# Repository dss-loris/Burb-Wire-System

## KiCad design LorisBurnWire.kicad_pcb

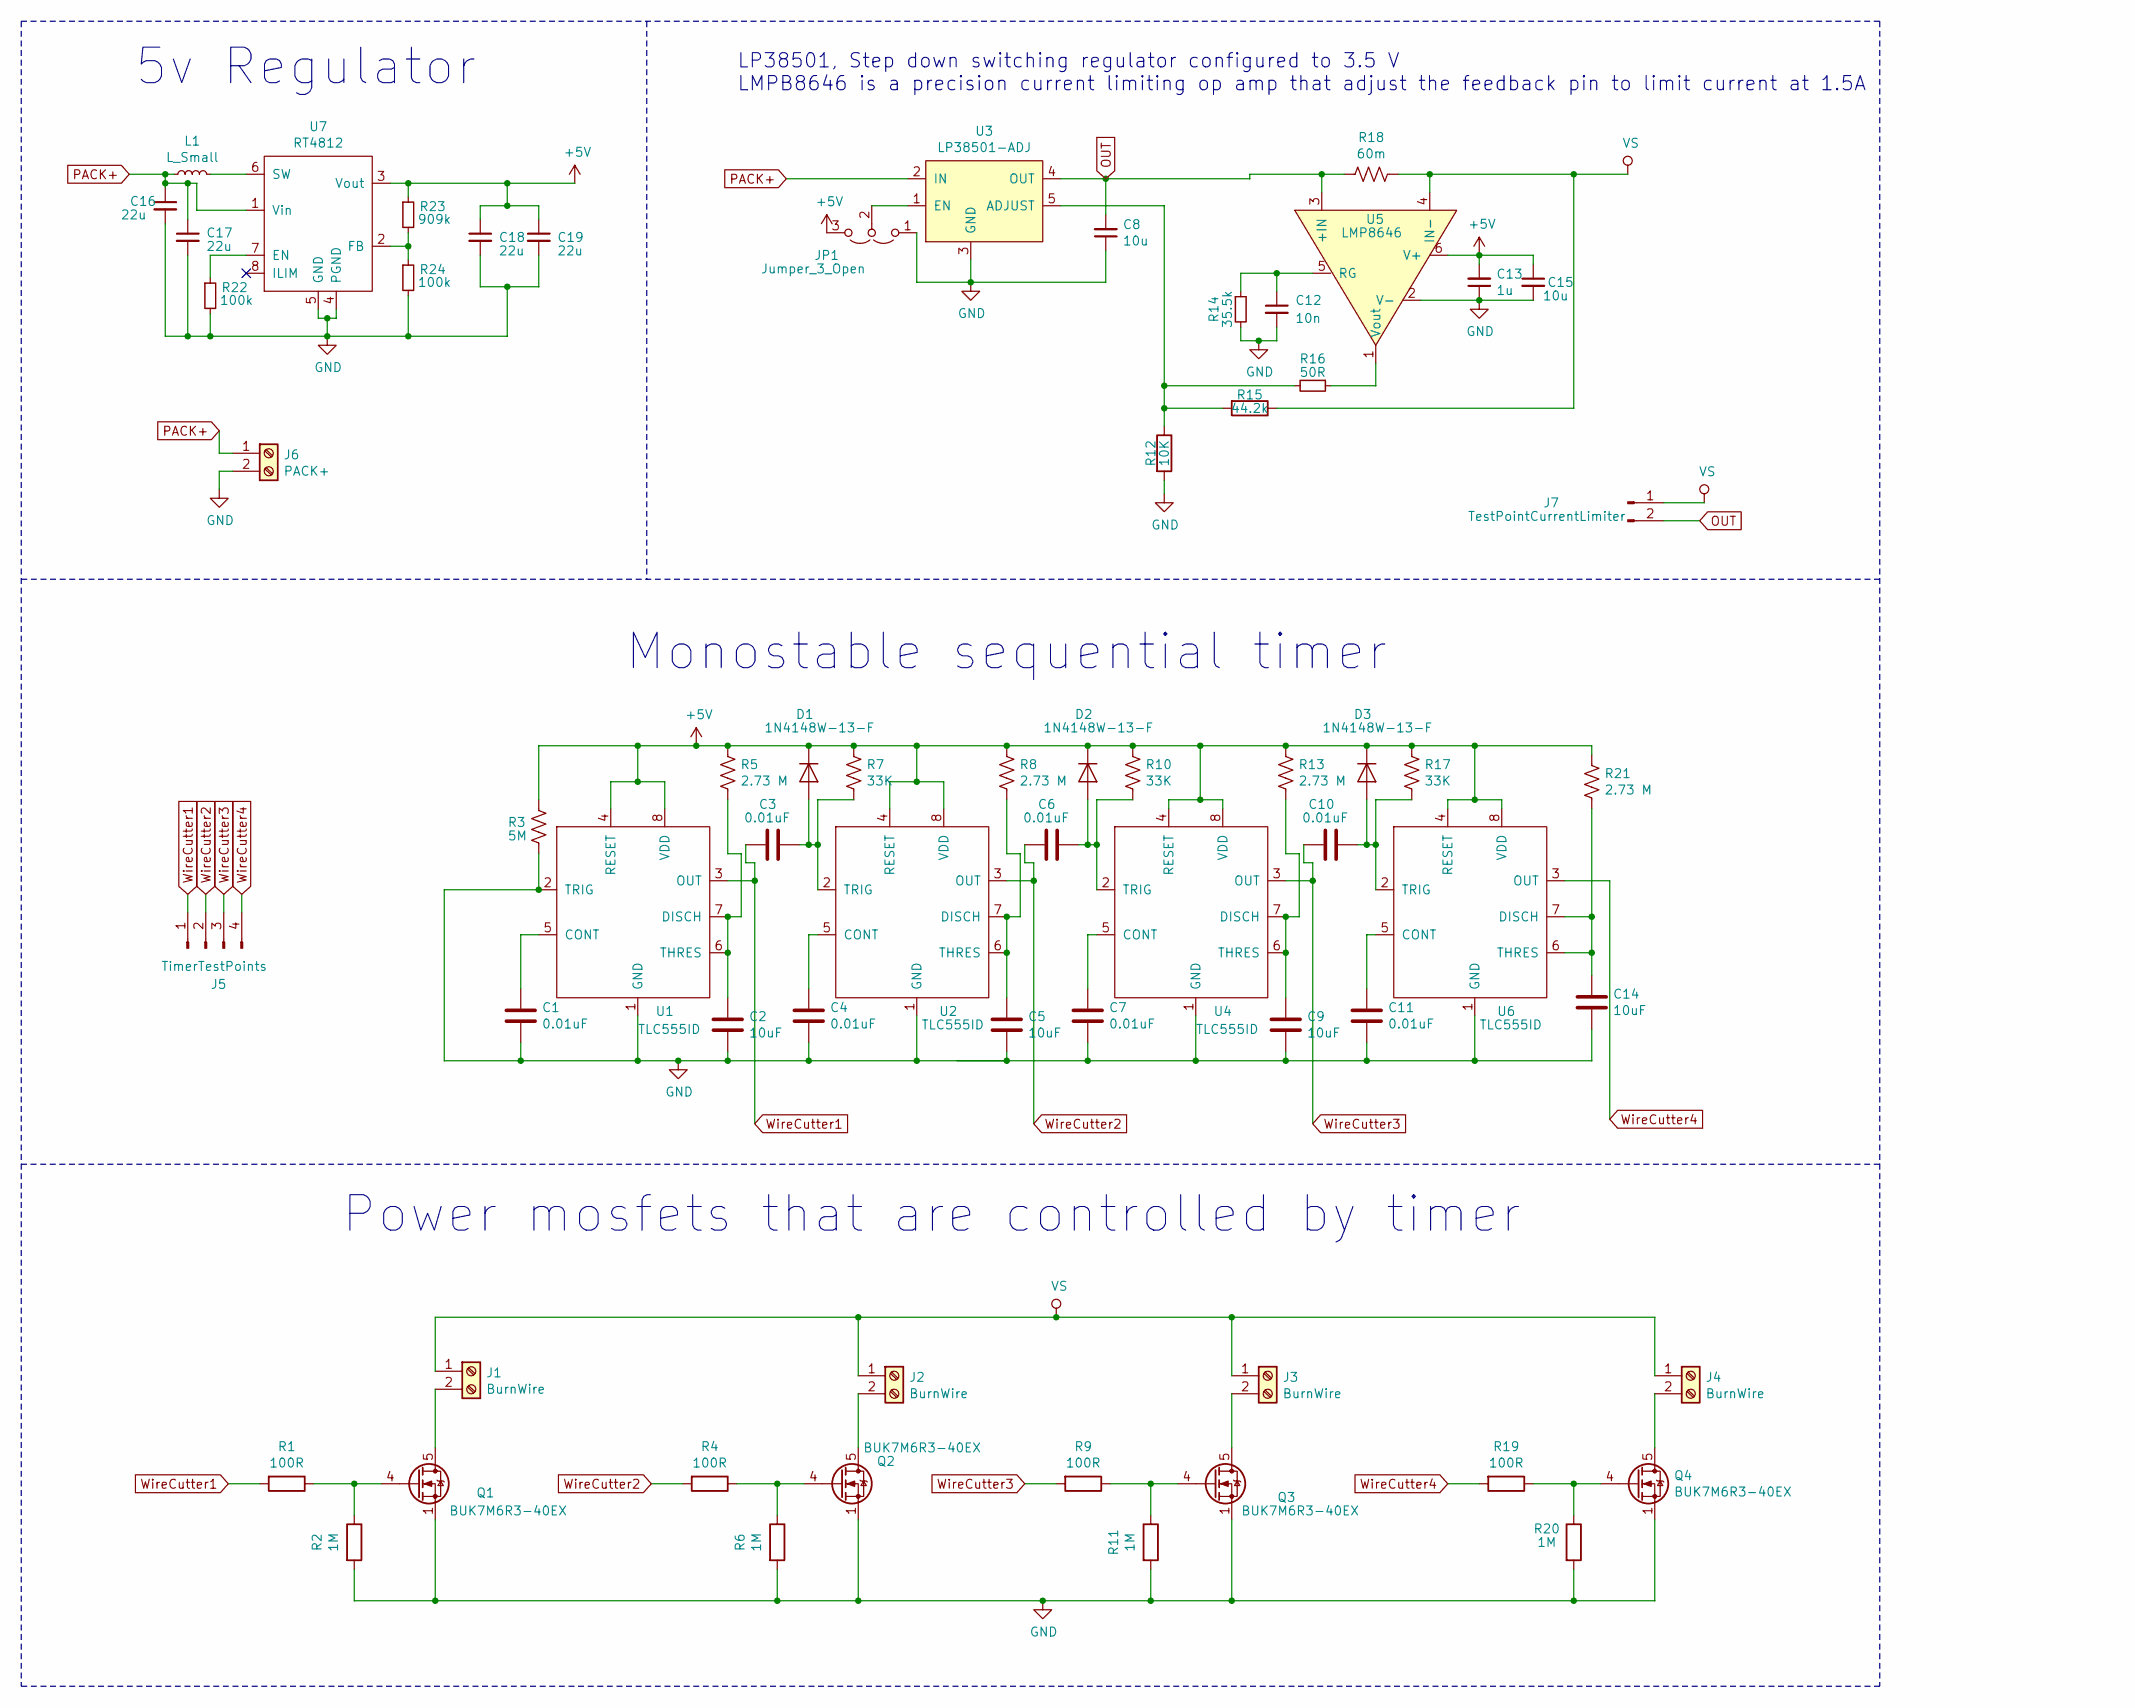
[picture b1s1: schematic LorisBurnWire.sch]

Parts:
C1, C3, C4, C6, C7, C10, C11: 0.01uF; C_1206_3216Metric_Pad1.42x1.75mm_HandSolder
C2, C5, C9, C14: 10uF; C_1206_3216Metric_Pad1.42x1.75mm_HandSolder
C8, C15: 10u; C_1206_3216Metric_Pad1.42x1.75mm_HandSolder
C12: 10n; C_1206_3216Metric_Pad1.42x1.75mm_HandSolder
C13: 1u; C_1206_3216Metric_Pad1.42x1.75mm_HandSolder
C16, C17, C18, C19: 22u; C_1206_3216Metric_Pad1.42x1.75mm_HandSolder
D1, D2, D3: 1N4148W-13-F; D_SOD-123
J1, J2, J3, J4: BurnWire; TE_282837-2
J5: TimerTestPoints; PinHeader_1x04_P2.54mm_Vertical
J6: PACK+; TE_282837-2
J7: TestPointCurrentLimiter; PinHeader_1x02_P2.54mm_Vertical
JP1: Jumper_3_Open; PinHeader_1x03_P2.54mm_Vertical
L1: L_Small; SPM6530T-3R3M; MFG Part Number SPM6530T-3R3M
Q1, Q2, Q3, Q4: BUK7M6R3-40EX; LFPAK33
R1, R4, R9, R19: 100R; R_1206_3216Metric_Pad1.42x1.75mm_HandSolder
R2, R6, R11, R20: 1M; R_1206_3216Metric_Pad1.42x1.75mm_HandSolder
R3: 5M; R_1206_3216Metric_Pad1.42x1.75mm_HandSolder
R5, R8, R13, R21: 2.73 M; R_1206_3216Metric_Pad1.42x1.75mm_HandSolder
R7, R10, R17: 33K; R_1206_3216Metric_Pad1.42x1.75mm_HandSolder
R12: 10K; R_1206_3216Metric_Pad1.42x1.75mm_HandSolder
R14: 35.5k; R_1206_3216Metric_Pad1.42x1.75mm_HandSolder
R15: 44.2k; R_1206_3216Metric_Pad1.42x1.75mm_HandSolder
R16: 50R; R_1206_3216Metric_Pad1.42x1.75mm_HandSolder
R18: 60m; R_1206_3216Metric_Pad1.42x1.75mm_HandSolder
R22, R24: 100k; R_1206_3216Metric_Pad1.42x1.75mm_HandSolder
R23: 909k; R_1206_3216Metric_Pad1.42x1.75mm_HandSolder
U1, U2, U4, U6: TLC555ID; SOIC-8_3.9x4.9mm_P1.27mm
U3: LP38501-ADJ; TO-263-5_TabPin3
U5: LMP8646; TSOT-23-6_HandSoldering
U7: RT4812; TSOT-23-8_HandSoldering

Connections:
+5V: C13.2, C15.1, C18.1, C19.1, D1.1 (K), D2.1 (K), D3.1 (K), JP1.3 (B), R3.1, R5.1, R7.1, R8.1, R10.1, R13.1, R17.1, R21.1, R23.1, U1.4 (RESET), U1.8 (VDD), U2.4 (RESET), U2.8 (VDD), U4.4 (RESET), U4.8 (VDD), U5.6 (V+), U6.4 (RESET), U6.8 (VDD), U7.3 (Vout)
GND: C1.2, C2.2, C4.2, C5.2, C7.2, C8.1, C9.2, C11.2, C12.2, C13.1, C14.2, C15.2, C16.2, C17.2, C18.2, C19.2, J6.2, JP1.1 (A), Q1.1 (S), Q1.2 (S), Q1.3 (S), Q2.1 (S), Q2.2 (S), Q2.3 (S), Q3.1 (S), Q3.2 (S), Q3.3 (S), Q4.1 (S), Q4.2 (S), Q4.3 (S), R2.2, R3.2, R6.2, R11.2, R12.2, R14.2, R20.2, R22.2, R24.2, U1.1 (GND), U1.2 (TRIG), U2.1 (GND), U3.3 (GND), U4.1 (GND), U5.2 (V-), U6.1 (GND), U7.4 (PGND), U7.5 (GND)
unnamed: C1.1, U1.5 (CONT)
unnamed: C2.1, R5.2, U1.6 (THRES), U1.7 (DISCH)
unnamed: C3.2, D1.2 (A), R7.2, U2.2 (TRIG)
unnamed: C4.1, U2.5 (CONT)
unnamed: C5.1, R8.2, U2.6 (THRES), U2.7 (DISCH)
unnamed: C6.2, D2.2 (A), R10.2, U4.2 (TRIG)
unnamed: C7.1, U4.5 (CONT)
unnamed: C9.1, R13.2, U4.6 (THRES), U4.7 (DISCH)
unnamed: C10.2, D3.2 (A), R17.2, U6.2 (TRIG)
unnamed: C11.1, U6.5 (CONT)
unnamed: C12.1, R14.1, U5.5 (RG)
unnamed: C14.1, R21.2, U6.6 (THRES), U6.7 (DISCH)
unnamed: J1.2, Q1.5 (D)
unnamed: J2.2, Q2.5 (D)
unnamed: J3.2, Q3.5 (D)
unnamed: J4.2, Q4.5 (D)
unnamed: JP1.2 (C), U3.1 (EN)
unnamed: L1.2, U7.6 (SW)
unnamed: Q1.4 (G), R1.1, R2.1
unnamed: Q2.4 (G), R4.1, R6.1
unnamed: Q3.4 (G), R9.1, R11.1
unnamed: Q4.4 (G), R19.1, R20.1
unnamed: R12.1, R15.2, R16.2, U3.5 (ADJUST)
unnamed: R16.1, U5.1 (Vout)
unnamed: R22.1, U7.7 (EN)
unnamed: R23.2, R24.1, U7.2 (FB)
OUT: C8.2, J7.2, R18.2, U3.4 (OUT), U5.3 (+IN)
PACK+: C16.1, C17.1, J6.1, L1.1, U3.2 (IN), U7.1 (Vin)
VS: J1.1, J2.1, J3.1, J4.1, J7.1, R15.1, R18.1, U5.4 (IN-)
WireCutter1: C3.1, J5.1, R1.2, U1.3 (OUT)
WireCutter2: C6.1, J5.2, R4.2, U2.3 (OUT)
WireCutter3: C10.1, J5.3, R9.2, U4.3 (OUT)
WireCutter4: J5.4, R19.2, U6.3 (OUT)

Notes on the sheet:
LP38501, Step down switching regulator configured to 3.5 V LMPB8646 is a precision current limiting op amp that adjust the feedback pin to limit current at 1.5A
Monostable sequential timer
Power mosfets that are controlled by timer
5v Regulator

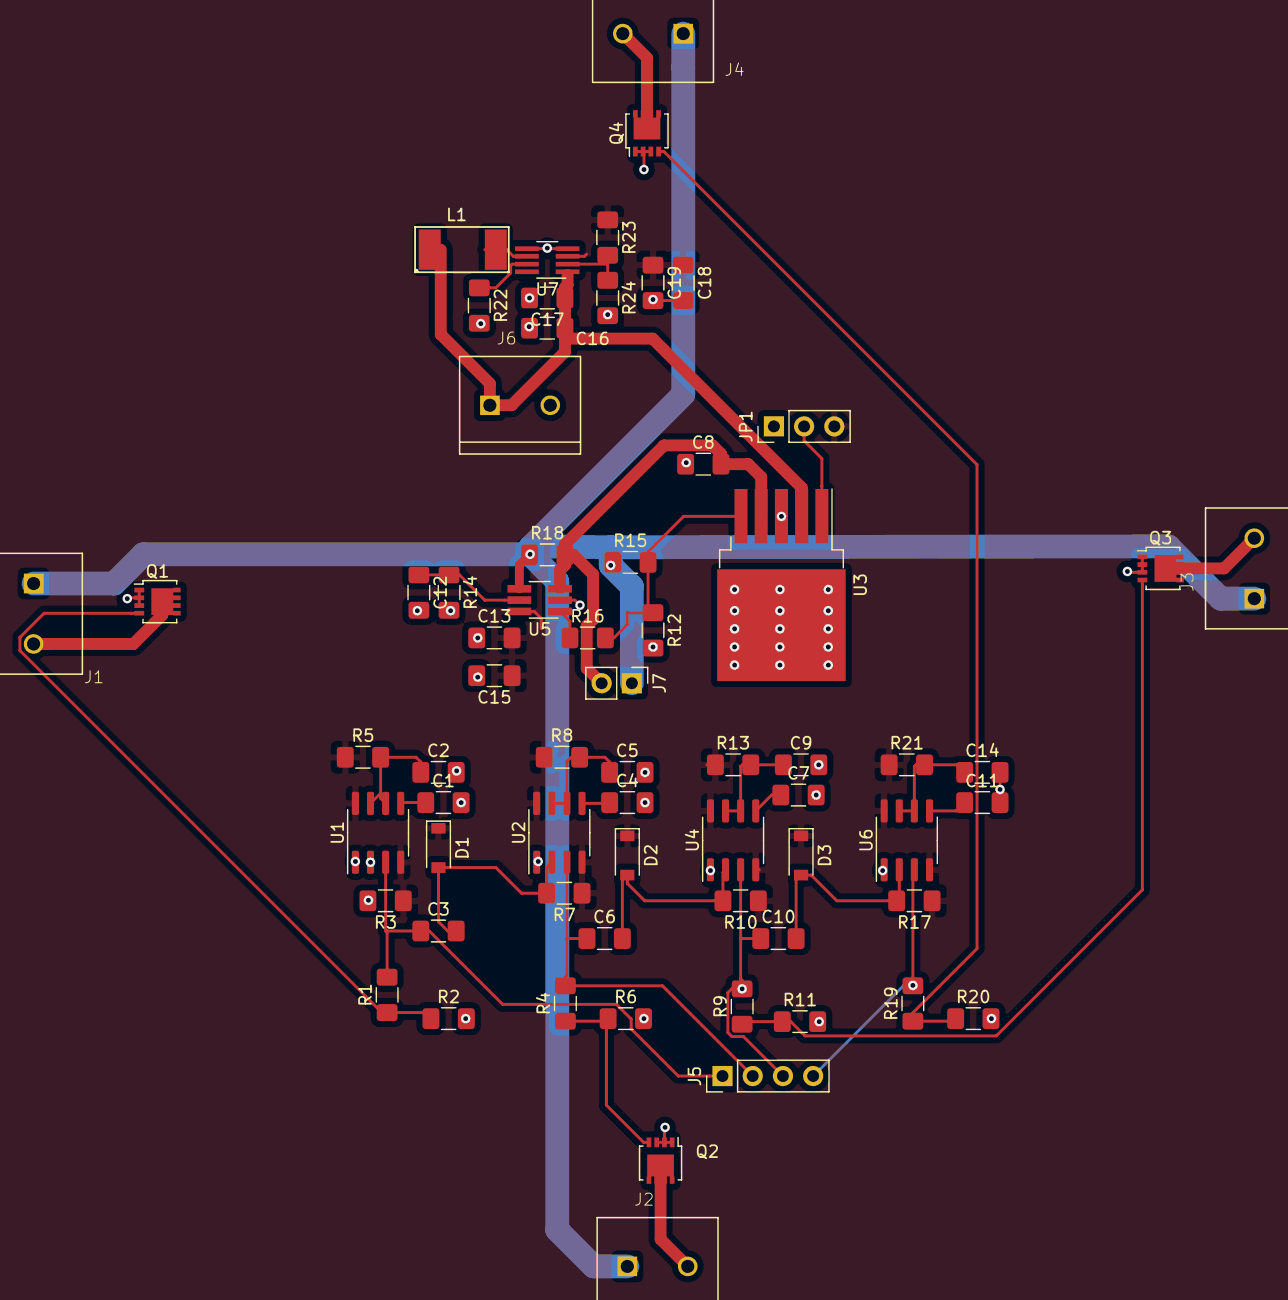
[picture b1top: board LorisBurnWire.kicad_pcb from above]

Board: 2 copper layers, 66 parts (0 on the bottom side), 35 nets.

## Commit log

2020-02-12 init_commit
2020-02-14 added_four_regulators
2020-02-14 added_bjt
2020-02-14 practice
2020-02-15 fixxed_error
2020-02-15 moddy
2020-02-25 started_pcb
2020-03-31 added precicion current limiter
2020-04-01 added powerfet
2020-04-01 fixed mistake
2020-04-06 added jumpers to turn regulator off and on
2020-04-22 added resistor to fets and added screw terminals
2020-04-22 added footprints to all the resistors and capacitors
2020-04-22 Added footprint to burn wires
2020-04-22 Fixed footprint applied to burnwire
2020-04-22 jumper wire footprint
2020-04-22 updated jumper wire footprint
2020-04-23 Added footprint to LMP8646
2020-04-24 added 5v regulator and finished adding footprints
2020-04-25 Initial work on PCB layout
2020-04-30 Rough layout of PCB
2020-05-05 edits
2020-05-06 changed trace width
2020-06-05 added simulation
2020-06-05 sims
2020-06-05 changes for owen
2020-06-05 New Timer Schematic based on LTC6993
2020-06-10 Switched to 2 timers instead of 4
